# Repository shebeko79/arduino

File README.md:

## Projects description
[Pulmonary Function Testing (PFT)](./pft)

[Car track using telegram bot](./car_dfrobot)

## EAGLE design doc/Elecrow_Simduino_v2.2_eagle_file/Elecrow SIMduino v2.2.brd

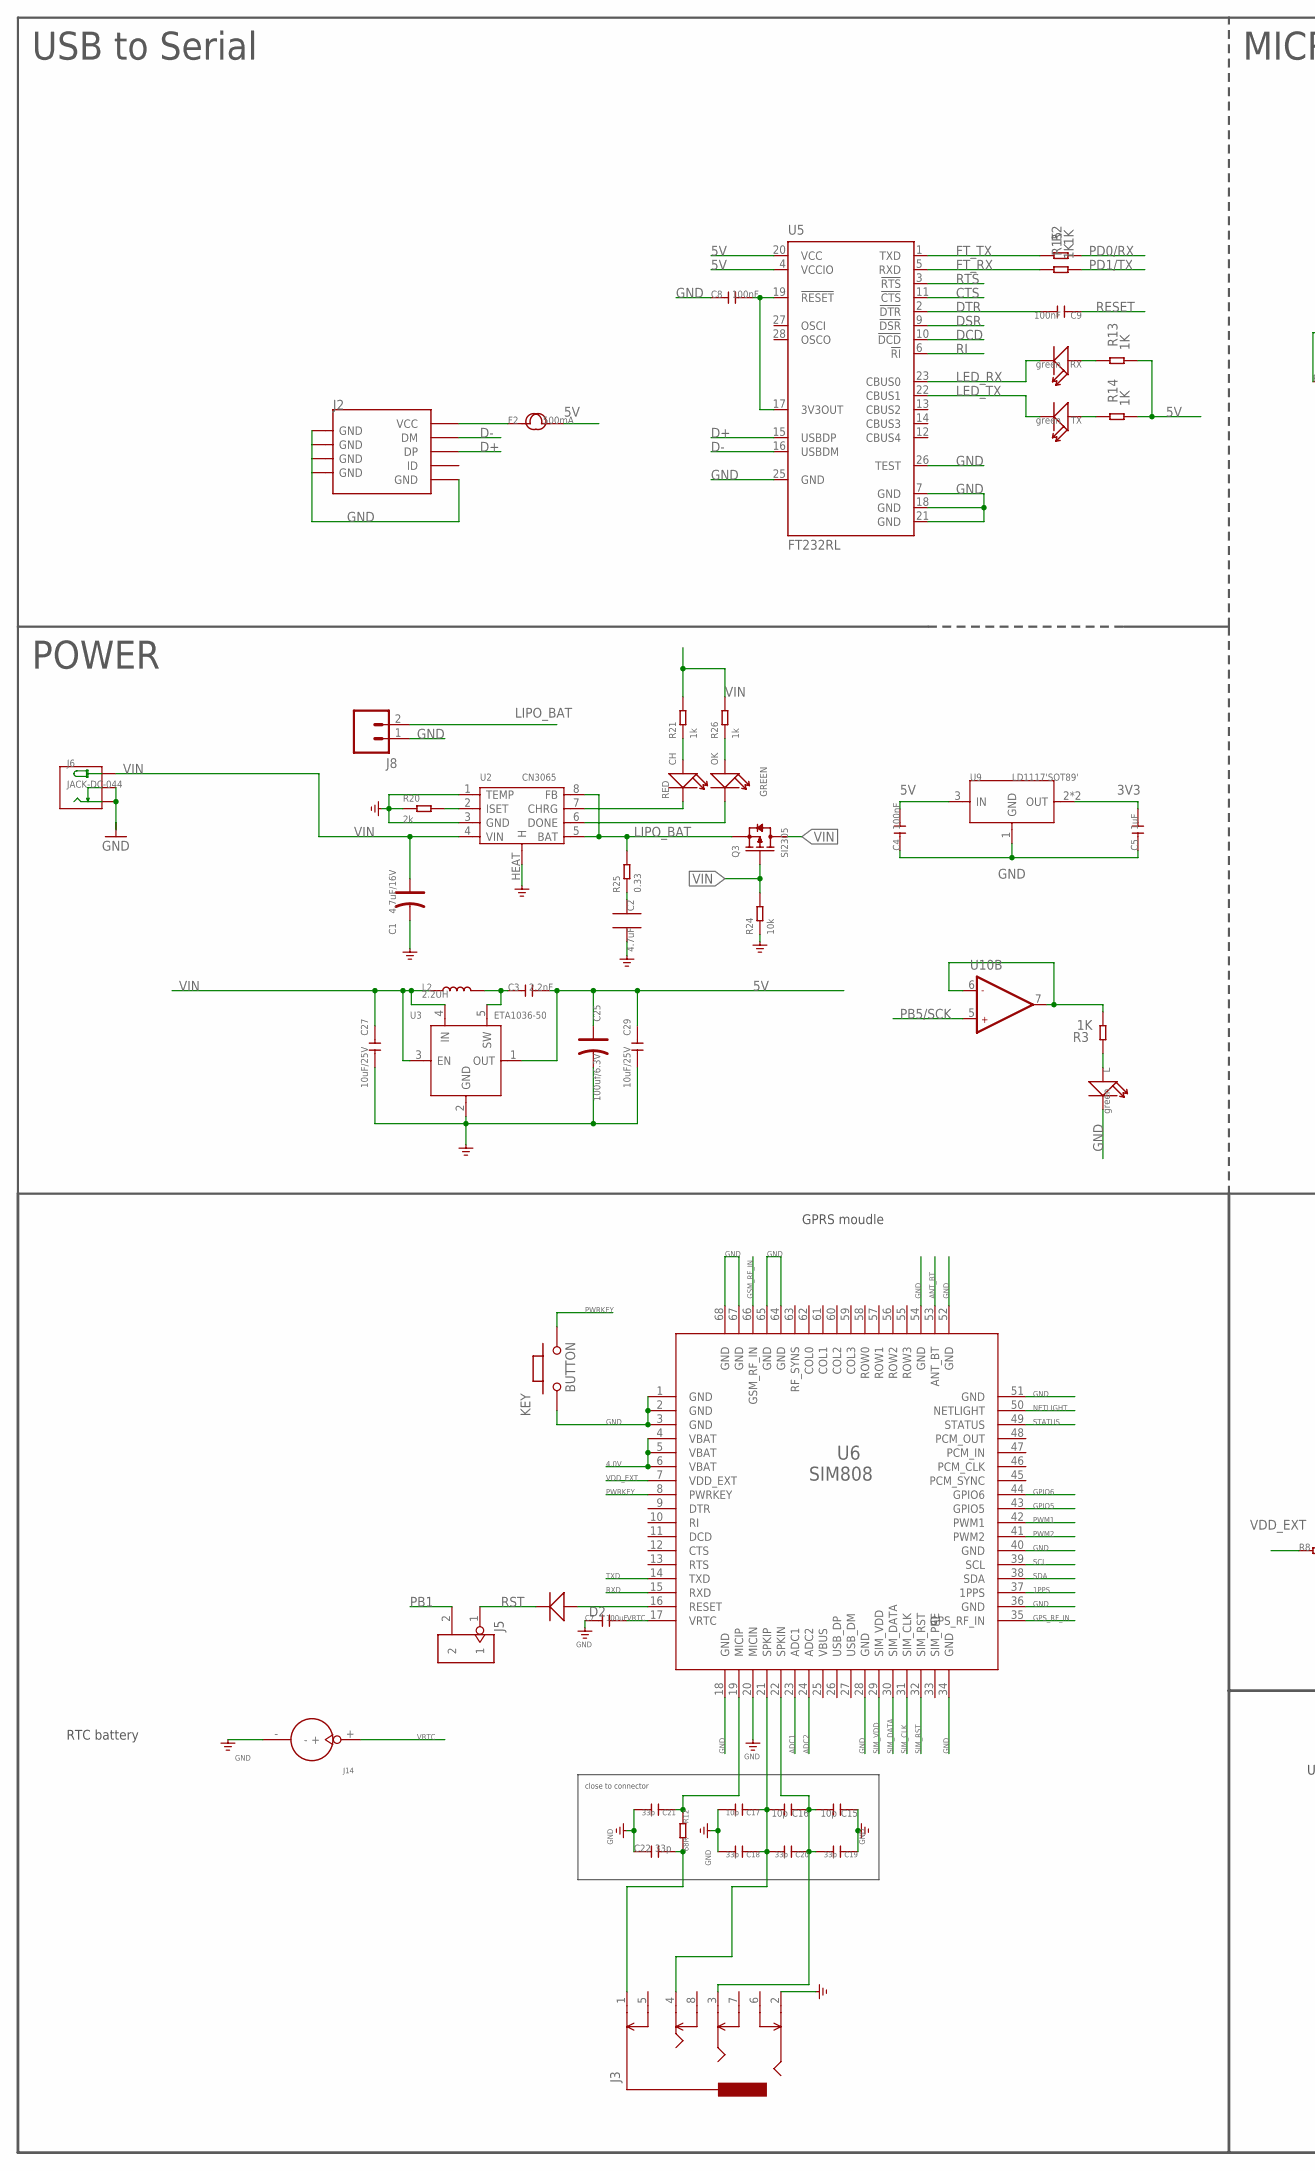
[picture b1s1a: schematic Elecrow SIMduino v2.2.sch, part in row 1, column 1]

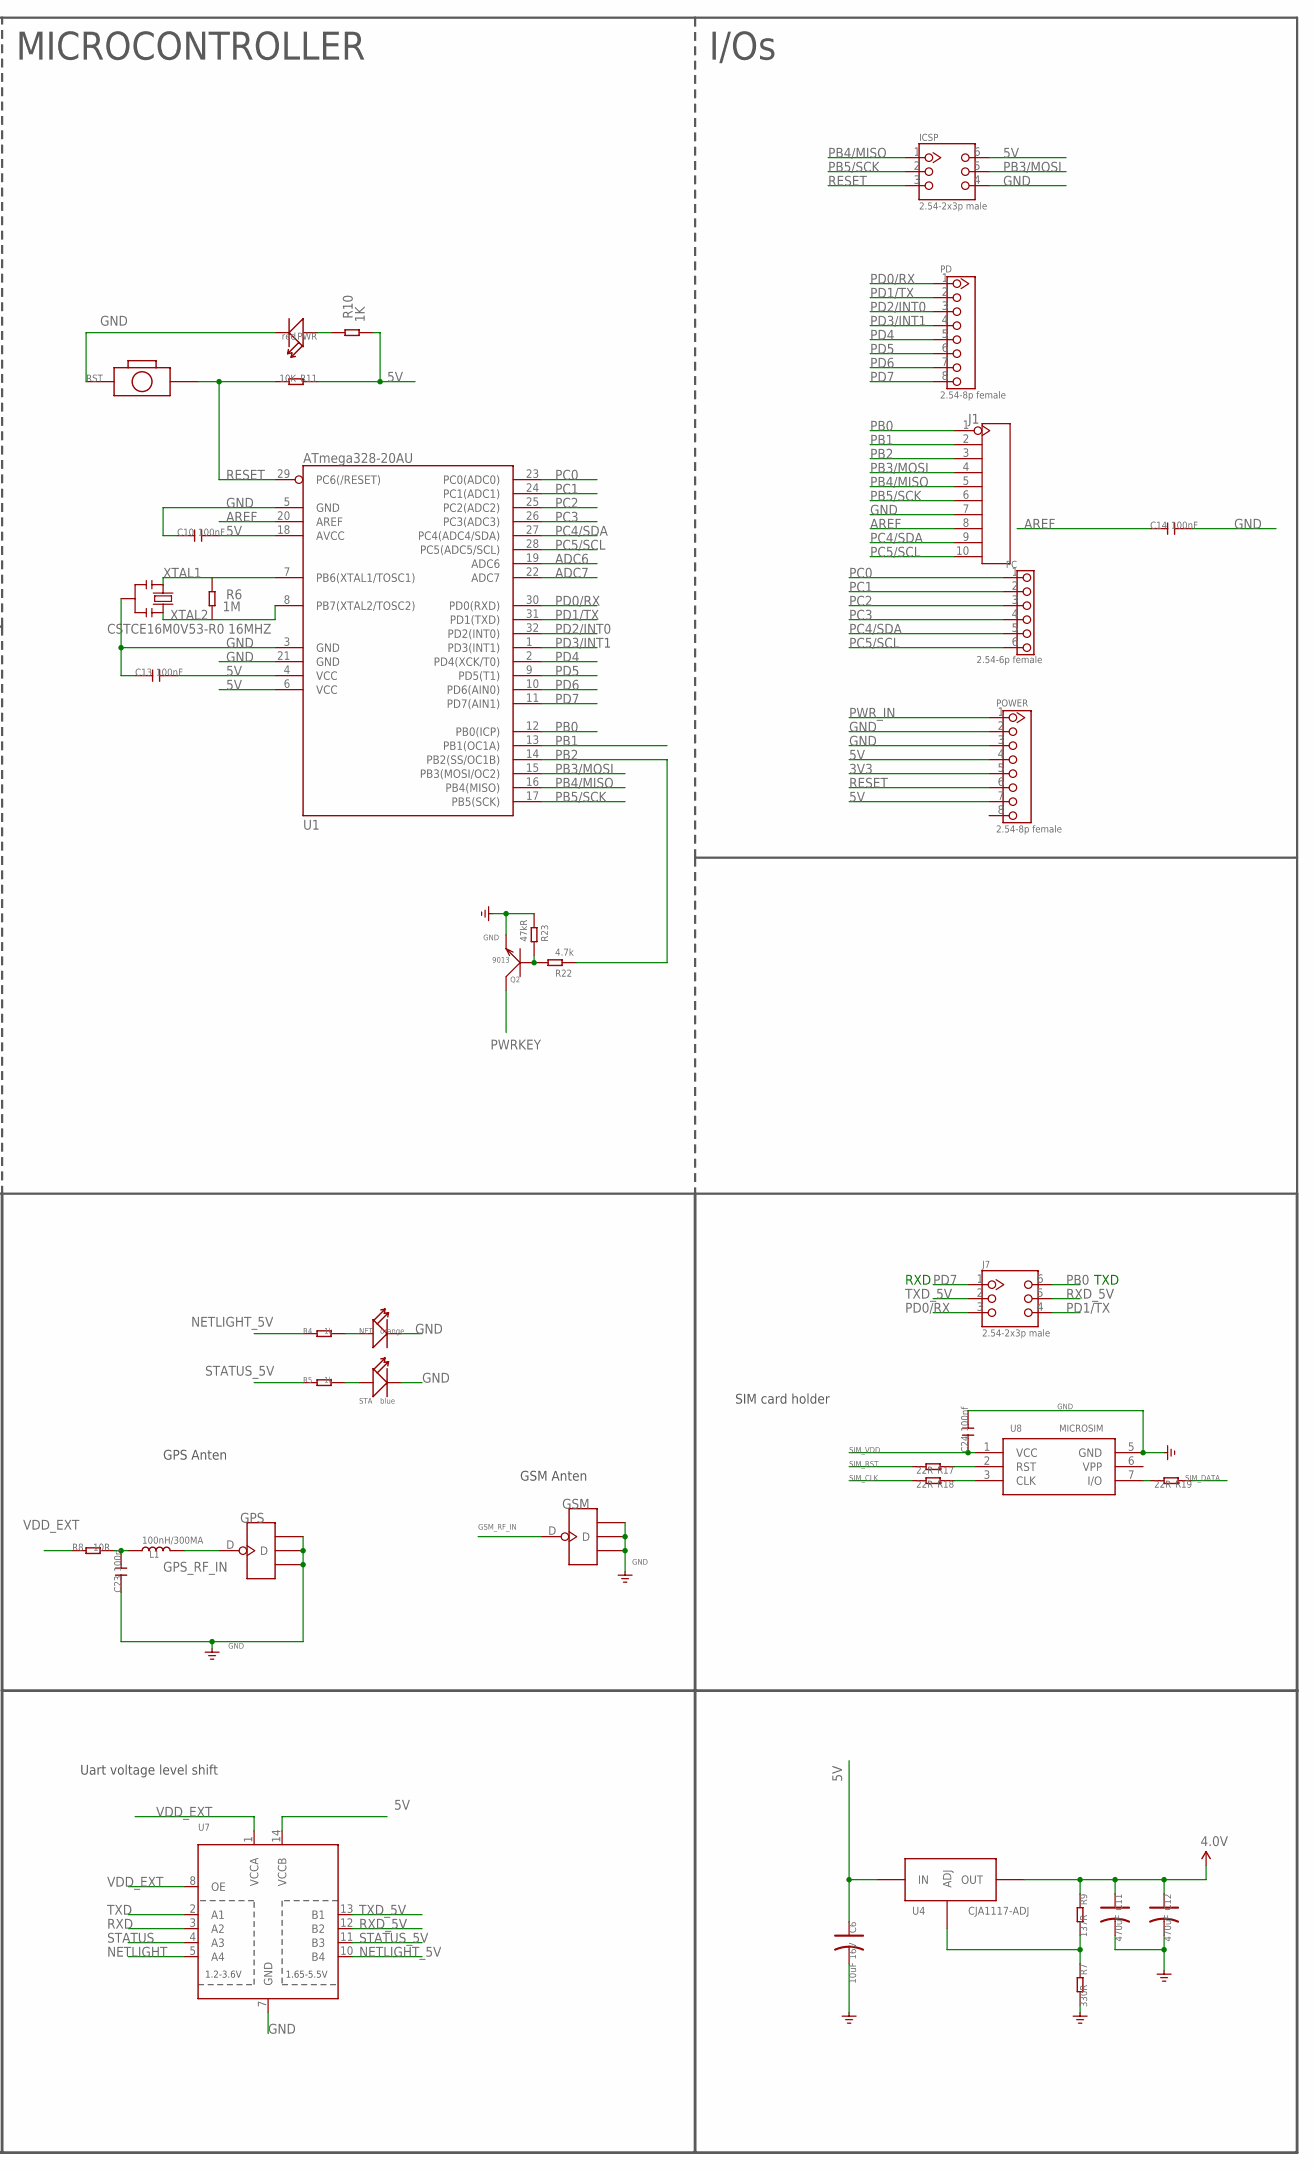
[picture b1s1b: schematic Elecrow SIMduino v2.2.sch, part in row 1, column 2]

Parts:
C1: 4.7uF/16V; AVX_A
C2: 4.7uF; 0805
C3: 2.2nF; C0603
C4, C8, C9, C10, C13, C14: 100nF; C0603
C5: 1uF; C0603
C6: 10uF 16V; AVX-A
C7: 100uF; C0805
C11, C12: 470uF; AVX-D
C15, C16, C17: 10p; C0402
C18, C19, C20: 33p; C0402
C21, C22: 33p; C0603
C23: 100n; C0603
C24: 100nf; C0603
C25: 100uf/6.3V; AVX-B
C27, C29: 10uF/25V; C0805
CH: RED; LED-0603
D2: D'0805'; SOD323
F2: 500mA; R1206@1
GPS: ANTENNA-U-FL; 4P-U-FL
GSM: ANTENNA-U-FL; 4P-U-FL
ICSP: 2.54-2x3p male; 2X3P-2.54
J1: HEADER-10P-2.54; 10P-2.54
J2: USB-MINIUSB-5P-STRONG; MINI-SMD-5P
J3: AUDIO-8P'PJ-3536-L6S'; 8P-3.5-SMD
J5: HEADER-2P-65/35MIL; 2P-2.54-65/35MIL
J6: JACK-DC-044; DC-404
J7: 2.54-2x3p male; 2X3P-2.54
J8: M02-JST-2MM-SMT; JST-2-SMD
J14: HOLDER-BATTERY-2P-CR1220; CR1220
KEY: BUTTON; 157SW
L: green; LED-0603
L1: 100nH/300MA; L0603
L2: 2.2UH; SD32-4R7MC
NET: orange; LED-0603
OK: GREEN; LED-0603
PC: 2.54-6p female; 6P-2.54-65/35MIL
PD: 2.54-8p female; 8P-2.54
POWER: 2.54-8p female; 8P-2.54
PWR: red; LED-0603
Q2: 9013; SOT23
Q3: SI2305; SOT-23
R2, R3, R10, R13, R14, R15: 1K; R0603
R4, R5, R21, R26: 1k; R0603
R6: 1M; R0603
R7: 330R; R0603
R8: 10R; R0603
R9: 137R; R0603
R11: 10K; R0603
R12: 68R; R0603
R17, R18, R19: 22R; R0603
R20: 2k; R0603
R22: 4.7k; R0402
R23: 47kR; R0402
R24: 10k; R0603
R25: 0.33; R0603
RST: BOTTON-2P-90D; 2P-7.62X3.56-90D
RX: green; LED-0603
STA: blue; LED-0603
TX: green; LED-0603
U1: ATmega328-20AU; TQFP32
U2: CN3065; DFN-8
U3: ETA1036-50; SOT23-5
U4: CJA1117-ADJ; SOT89
U5: FT232RL; SSOP28
U6: SIM808
U7: TXB0104PWR; TSSOP14
U8: MICROSIM
U9: LD1117'SOT89'; SOT89
U10: LMV358DGK; MSOP8
Y2: CSTCE16M0V53-R0 16MHZ; RESONATOR

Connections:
1PPS: U6.37 (1PPS)
3V3: C5.2, POWER.5, U9.2 (OUT), U9.4 (OUT)
4.0V: C11.+, C12.+, R9.1, U4.2 (OUT), U4.4 (OUT), U6.4 (VBAT), U6.5 (VBAT), U6.6 (VBAT)
5V: C3.2, C4.2, C6.+, C10.2, C13.2, C25.+, C29.1, F2.2, ICSP.6, POWER.4, POWER.7, R10.1, R11.1, R13.1, R14.1, U1.4 (VCC), U1.6 (VCC), U1.18 (AVCC), U3.1 (OUT), U4.3 (IN), U5.4 (VCCIO), U5.20 (VCC), U7.14 (VCCB), U9.3 (IN)
+V: U10.8 (+V)
ADC1: U6.23 (ADC1)
ADC2: U6.24 (ADC2)
ADC6: U1.19 (ADC6)
ADC7: U1.22 (ADC7)
ANT_BT: U6.53 (ANT_BT)
AREF: C14.1, J1.8, U1.20 (AREF)
COL0: U6.62 (COL0)
COL1: U6.61 (COL1)
COL2: U6.60 (COL2)
COL3: U6.59 (COL3)
CTS: U5.11 (!CTS)
D+: J2.3 (DP), U5.15 (USBDP)
D-: J2.2 (DM), U5.16 (USBDM)
DCD: U5.10 (!DCD)
DSR: U5.9 (!DSR)
DTR: C9.2, U5.2 (!DTR)
FT_RX: R15.2, U5.5 (RXD)
FT_TX: R2.2, U5.1 (TXD)
GND: C1.-, C2.2, C4.1, C5.1, C6.-, C7.1, C8.1, C10.1, C11.-, C12.-, C13.1, C14.2, C15.1, C17.2, C18.2, C19.1, C21.2, C22.1, C23.1, C24.2, C25.-, C27.2, C29.2, GPS.GND1, GPS.GND2, GPS.GND3, GSM.GND1, GSM.GND2, GSM.GND3, ICSP.4, J1.7, J2.5 (GND), J2.GND@1 (GND), J2.GND@2 (GND), J2.GND@3 (GND), J2.GND@4 (GND), J3.2, J6.-, J6.CDN, J8.1, J14.-, KEY.1, L.-, NET.-, POWER.2, POWER.3, PWR.-, Q2.2 (E), R7.2, R20.1, R23.1, R24.1, RST.P$1 (1), STA.-, U1.3 (GND), U1.5 (GND), U1.21 (GND), U2.1 (TEMP), U2.3 (GND), U2.HEAT (H), U3.2 (GND), U5.7 (GND), U5.18 (GND), U5.21 (GND), U5.25 (GND), U5.26 (TEST), U6.1 (GND), U6.2 (GND), U6.3 (GND), U6.18 (GND), U6.20 (MICIN), U6.28 (GND), U6.34 (GND), U6.36 (GND), U6.40 (GND), U6.51 (GND), U6.52 (GND), U6.54 (GND), U6.64 (GND), U6.65 (GND), U6.67 (GND), U6.68 (GND), U7.7 (GND), U8.5 (GND), U9.1 (GND), U10.4 (GND), Y2.2
GPIO5: U6.43 (GPIO5)
GPIO6: U6.44 (GPIO6)
GPS_RF_IN: GPS.D, L1.2, U6.35 (GPS_RF_IN)
GSM_RF_IN: GSM.D, U6.66 (GSM_RF_IN)
LED_RX: RX.-, U5.23 (CBUS0)
LED_TX: TX.-, U5.22 (CBUS1)
LIPO_BAT: J8.2, Q3.2 (S), R25.2, U2.5 (BAT), U2.8 (FB)
unnamed: R20.2, U2.2 (ISET)
unnamed: R13.2, RX.+
unnamed: L.+, R3.2
unnamed: R5.2, STA.+
unnamed: R3.1, U10.6 (-IN2), U10.7 (OUT2)
unnamed: C8.2, U5.17 (3V3OUT), U5.19 (!RESET)
unnamed: PWR.+, R10.2
unnamed: R14.2, TX.+
unnamed: F2.1, J2.1 (VCC)
unnamed: NET.+, R4.2
unnamed: R18.1, U8.3 (CLK)
unnamed: R17.1, U8.2 (RST)
unnamed: C21.1, R12.1, U6.19 (MICIP)
unnamed: C16.2, C17.1, C18.1, C20.2, J3.4, U6.21 (SPKIP)
unnamed: R19.2, U8.7 (I/O)
unnamed: R7.1, R9.2, U4.1 (ADJ)
unnamed: D2.+, U6.16 (RESET)
unnamed: C15.2, C16.1, C19.2, C20.1, J3.3, U6.22 (SPKIN)
unnamed: CH.-, U2.7 (CHRG)
unnamed: C23.2, L1.1, R8.2
unnamed: OK.-, U2.6 (DONE)
unnamed: OK.+, R26.1
unnamed: C2.1, R25.1
unnamed: CH.+, R21.1
unnamed: C3.1, L2.2, U3.5 (SW)
unnamed: C22.2, J3.1, R12.2
unnamed: Q2.1 (B), R22.2, R23.2
NETLIGHT: U6.50 (NETLIGHT), U7.5 (A4)
NETLIGHT_5V: R4.1, U7.10 (B4)
PB0: J1.1, J7.6, U1.12 (PB0(ICP))
PB1: J1.2, J5.2, U1.13 (PB1(OC1A))
PB2: J1.3, R22.1, U1.14 (PB2(SS/OC1B))
PB3/MOSI: ICSP.5, J1.4, U1.15 (PB3(MOSI/OC2))
PB4/MISO: ICSP.1, J1.5, U1.16 (PB4(MISO))
PB5/SCK: ICSP.2, J1.6, U1.17 (PB5(SCK)), U10.5 (+IN2)
PC0: PC.1, U1.23 (PC0(ADC0))
PC1: PC.2, U1.24 (PC1(ADC1))
PC2: PC.3, U1.25 (PC2(ADC2))
PC3: PC.4, U1.26 (PC3(ADC3))
PC4/SDA: J1.9, PC.5, U1.27 (PC4(ADC4/SDA))
PC5/SCL: J1.10, PC.6, U1.28 (PC5(ADC5/SCL))
PD0/RX: J7.3, PD.1, R2.1, U1.30 (PD0(RXD))
PD1/TX: J7.4, PD.2, R15.1, U1.31 (PD1(TXD))
PD2/INT0: PD.3, U1.32 (PD2(INT0))
PD3/INT1: PD.4, U1.1 (PD3(INT1))
PD4: PD.5, U1.2 (PD4(XCK/T0))
PD5: PD.6, U1.9 (PD5(T1))
PD6: PD.7, U1.10 (PD6(AIN0))
PD7: J7.1, PD.8, U1.11 (PD7(AIN1))
PWM1: U6.42 (PWM1)
PWM2: U6.41 (PWM2)
PWRKEY: KEY.2, Q2.3 (C), U6.8 (PWRKEY)
PWR_IN: POWER.1
RESET: C9.1, ICSP.3, POWER.6, R11.2, RST.P$2 (2), U1.29 (PC6(/RESET))
RF_SYNS: U6.63 (RF_SYNS)
RI: U5.6 (!RI)
ROW0: U6.58 (ROW0)
ROW1: U6.57 (ROW1)
ROW2: U6.56 (ROW2)
ROW3: U6.55 (ROW3)
RST: D2.-, J5.1
RTS: U5.3 (!RTS)
RXD: U6.15 (RXD), U7.3 (A2)
RXD_5V: J7.5, U7.12 (B2)
SCL: U6.39 (SCL)
SDA: U6.38 (SDA)
SIM_CLK: R18.2, U6.31 (SIM_CLK)
SIM_DATA: R19.1, U6.30 (SIM_DATA)
SIM_RST: R17.2, U6.32 (SIM_RST)
SIM_VDD: C24.1, U6.29 (SIM_VDD), U8.1 (VCC)
STATUS: U6.49 (STATUS), U7.4 (A3)
STATUS_5V: R5.1, U7.11 (B3)
TXD: U6.14 (TXD), U7.2 (A1)
TXD_5V: J7.2, U7.13 (B1)
VDD_EXT: R8.1, U6.7 (VDD_EXT), U7.1 (VCCA), U7.8 (OE)
VIN: C1.+, C27.1, J6.+, L2.1, Q3.1 (G), Q3.3 (D), R21.2, R24.2, R26.2, U2.4 (VIN), U3.3 (EN), U3.4 (IN)
VRTC: C7.2, J14.+, U6.17 (VRTC)
XTAL1: R6.2, U1.7 (PB6(XTAL1/TOSC1)), Y2.1
XTAL2: R6.1, U1.8 (PB7(XTAL2/TOSC2)), Y2.3

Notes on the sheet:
USB to Serial
POWER
MICROCONTROLLER
I/Os
close to connector
GPRS moudle
GPS Anten
GSM Anten
Uart voltage level shift
SIM card holder
TXD
RXD
RTC battery

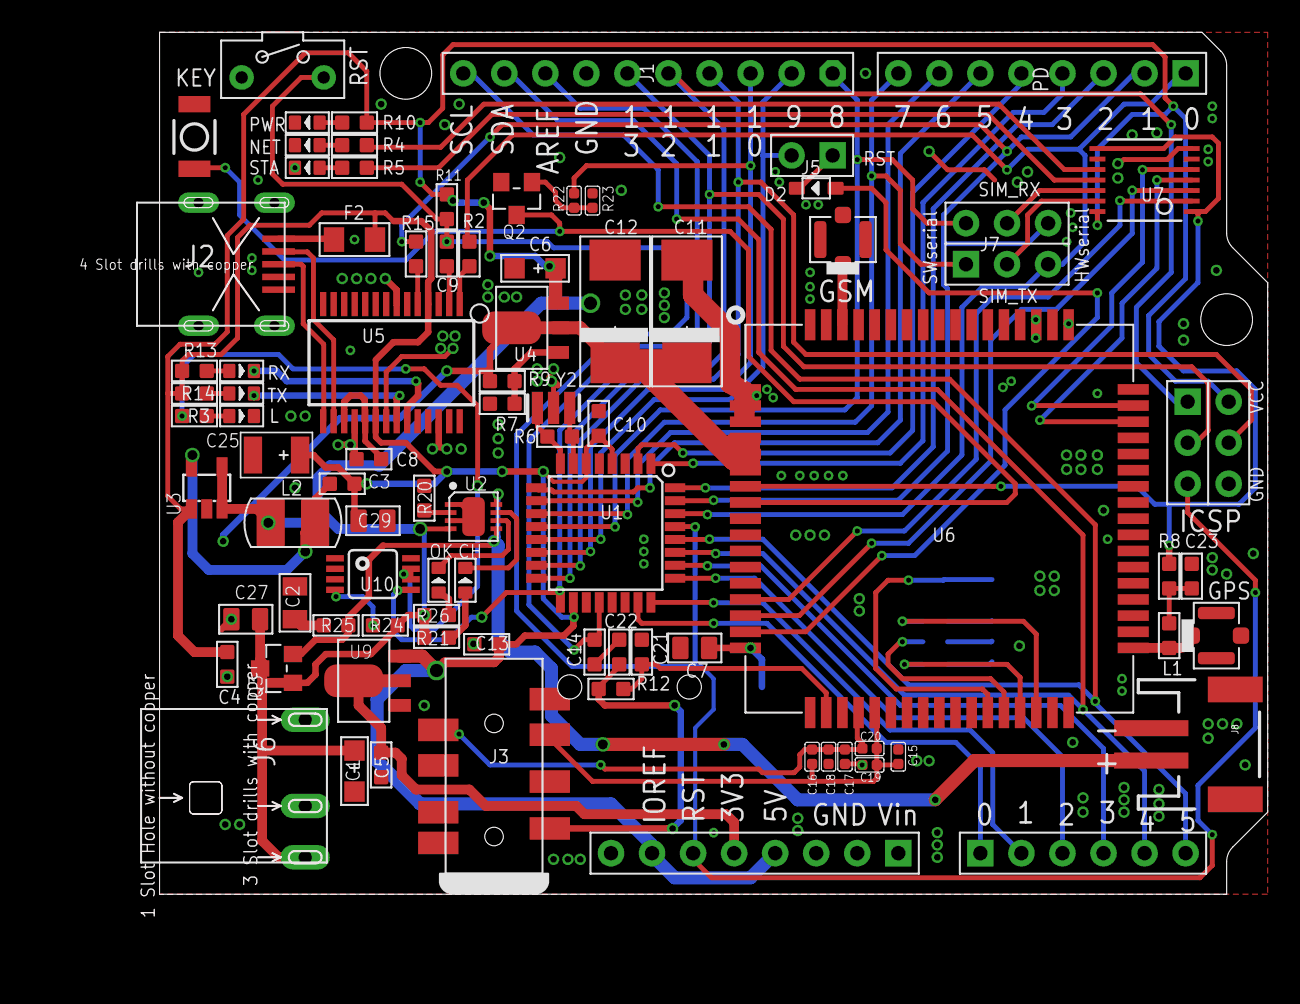
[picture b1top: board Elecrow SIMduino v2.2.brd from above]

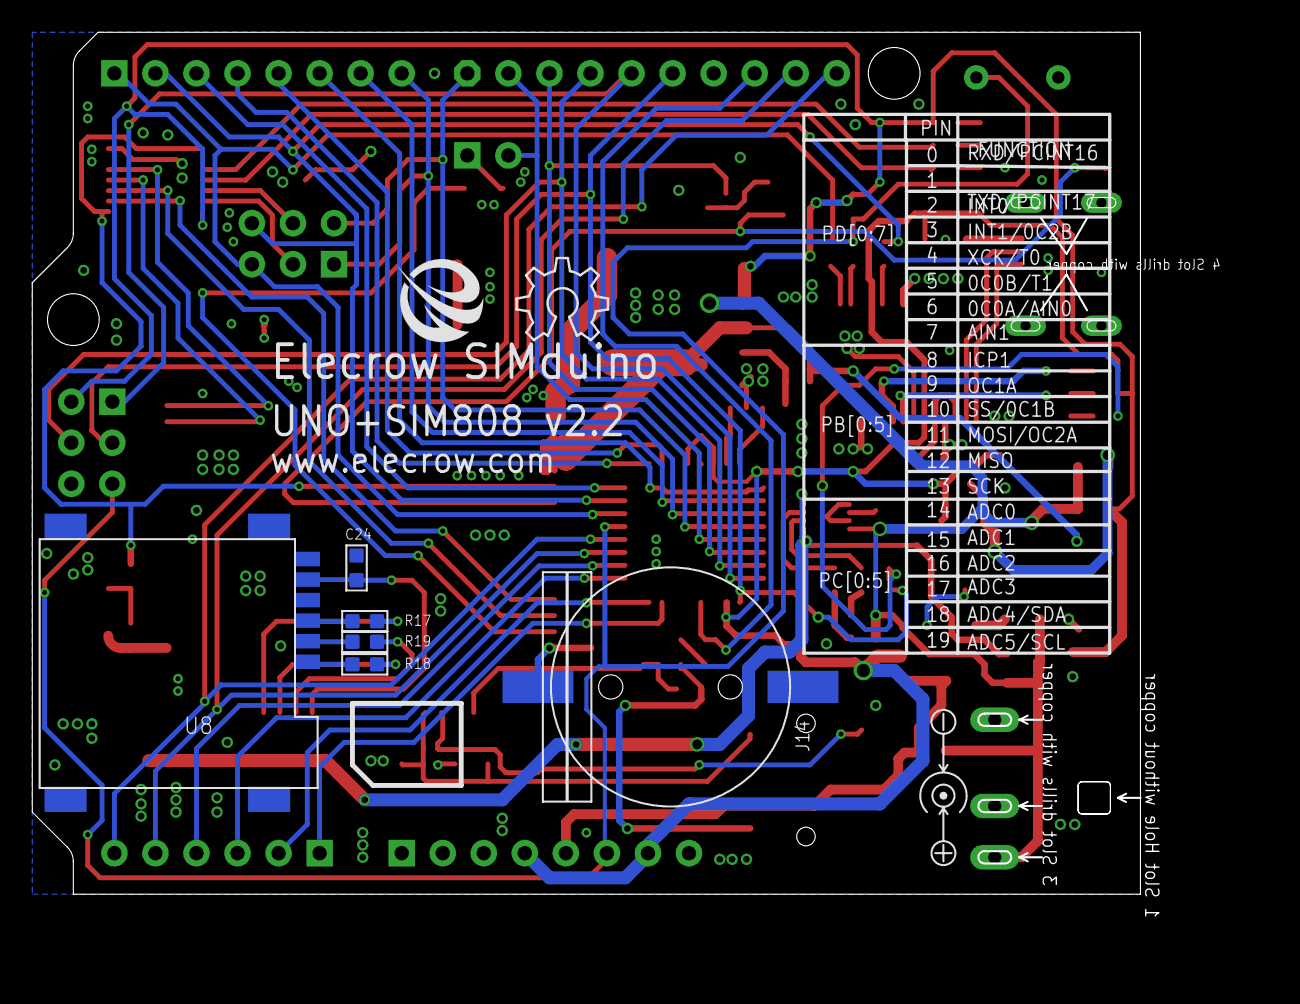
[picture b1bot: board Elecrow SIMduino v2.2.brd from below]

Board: 2 copper layers, 68.6 x 53.3 mm, 94 parts (8 on the bottom side), 82 nets.

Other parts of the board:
U$1: OSHW_6X200_NOTEXT
U$2: ELECROW-NEW

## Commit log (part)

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2021-11-11 add chicken
2021-11-11 add tests
2021-11-11 add doc
2021-11-11 add dachagaraz
2021-11-11 commit others projects
2021-11-11 CmAlarm
2021-12-26 Recover after WiFi failures. Silent messages. Temp sensor temporary doesn't work
2021-12-26 gitignore
2021-12-26 wire_length
2021-12-26 change for esp32
2021-12-26 udp_client
2023-01-16 Add scheme of uno sim800 board
2023-01-17 Files w/o secret keys
2023-02-15 SIM7000 car tracking version
2023-02-15 less debug information
2023-02-15 Just AT command list. Useful for troubleshooting.
2024-03-22 Pulmonary function tests
2024-03-22 Better touch screen interraction Better graph
2024-03-23 ticks[] calculated just in timer scale chart to actual data print seconds in x axis
2024-04-11 Draw battery status
2024-04-11 Add 3d model
2024-04-13 1. Result number on a different screen. 2. Add sleep mode. Sleep mode note that effective, device still consume 8mA so we still need physical power button
2024-04-13 1. Reduce mundshtuk size 2. Add cover to hide electronics
2024-04-13 Add *.blend1 to gitignore
2024-04-13 1. Move tick counter from timer isr to pin isr 2. Reduce scale because free spin was physically removed 3. Shortest scale must be not shorter than 1 second
2024-04-19 Draw total air-flow Draw FVC,FEV1,FEV1/FVC in the results
2024-04-20 Add license and readme
2024-04-20 Add references
2024-04-20 Fix spelling in README.md
2024-04-20 Add demo video to README.md
2024-04-20 Images of device
2024-04-20 Reduce images size
2024-04-20 Add images to README.md
2024-08-30 2 wheel platform based on esp32
2024-09-11 SIM7070 documentation
2024-09-11 Use macro for telegram chat id
2024-09-11 Test sim7070 AT commands sequence
2024-09-11 1. Save certificate into modem 2. Just regular AT terminal
2024-09-11 Prepare for modem replacement Isolate modem header
2024-09-11 Add sim7070.h
2024-09-13 Same speed as debug in car_dfrobot
2024-09-13 Remove comments
2024-09-13 1. Use F() macro to store strings in PROGMEM 2. Rewrite for HTTPS. Still need to debug.
2024-09-13 GPS can't work at the same time with mobile network. See https://stackoverflow.com/questions/61857667/sim7080g-module-cant-send-data-over-tcp-while-using-gnss
    That's why we must switch off GPS and then send data.
    For the same reason we can't keep HTTPS connection and have to open it again for each request.
2024-09-13 1. Read receive buffer chunk-by-chunk 2. use separate buffer for telegram, because modem_answer overrides by commands 3. Push 2 message at start, because first lost anyway 4. Commented out unnecessar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
2024-09-15 Overall projects readme
2024-09-20 Bluetooth remote control
2024-09-28 Add "block" command in BT remote control
2024-09-28 Examples files for maixcam
2024-10-05 Implementing state machine for UI
2024-10-06 Implement button click and rectangle selection
2024-10-06 Add rectangle normalization
2024-10-07 Add MoveTo algo.
2024-10-12 returns image each second on web
2024-10-12 Add buttons using ChatGPT
2024-10-12 ChatGPT button click handler
2024-10-12 chatGPT image click
2024-10-12 chatGPT select rectangle
2024-10-12 1. Prevent rectangle visible until object selection (chatGPT) 2. Prevent dragging image (chatGPT) 3. Process requests on server side 4. Prevent crash, when to_jpeg() returns None after script restart
2024-10-12 Add just move states
2024-10-13 Mobile adaptation for select rectangle (chatGPT)
2024-10-13 Click on image for mobile (chatGPT)
2024-10-13 Move buttons to right
2024-10-13 Rename move states for vertical alignment Load main html from BASE_PATH path
2024-10-15 Add WiFi features. If fail connect to WiFi switch to AP mode
2024-10-16 Disable wifi switch AP mode doesn't start DHCP And switch back to STA go wrong.
2024-10-19 Configuring network thru python was bad idea. Add S30wifidyn which try establish sta connection, if fails switch to ap mode
2024-10-19 Shrink move state to fit on a screen More robust S81robot stop function
2024-10-27 1. Get rid of Flask, because it creates a lot of threads and to noisy 2. Implement synchronized function call in main thread. 3. Get state just after click,click_point, sel_rect requests
2024-10-27 1. Apply immediately /click /click_point /sel_rect to buttons state 2. Return state even if requests are not executed 3. Move server to 80 port
2024-11-09 Increase line width to avoid red-grey rectangles
2024-11-19 pan\tilt stl model
2024-12-08 Parts schematic
2024-12-08 Test of zs-x11h controller
2024-12-09 rename motor.h to mdd3a controller which was used to control dc motor
2024-12-09 Add szx11h motor controller
2024-12-10 1. Move to PlatformIO 2. Speed measurement
2024-12-11 Connect brake pin
2024-12-12 Add PID control
2024-12-12 Change remote to relative protocol
2024-12-12 Add relative protocol
2024-12-13 1. Always brake for zero speed 2. 20kHz PWM just follow controllers recommendations 3. Separate RELATIVE_MAX_SPEED because it a bit scary with full speed 4. Dump wheels state in com port to have a gl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
2024-12-13 command to set maximum relative_speed
2024-12-13 Better command parsing
2024-12-21 Update 3d models 1. Base for pantilt 2. Cover for 2020 profile
2024-12-21 shorter screw placeholer
2024-12-25 Move servo closer to the front
2024-12-25 Maixcam pinout
2024-12-28 Fix rotation cast
2024-12-28 Change mover to speed and pan
2024-12-31 Add scservo_sdk and pan_tilt example proba/pan_tilt.py all necessary function (i.e. reduce baud rate) which performes thru USB of SCServo controller maix/pan_tilt.py is a sketch for pan-til support
2025-01-01 Implementation of pan-tilt tracking Doesn't work as expected yet
2025-01-01 Add exit state for graceful exit
2025-01-02 Release servos when exit Measure real focus distance
2025-01-04 Full screen image
2025-01-05 1. Use relative (0.0-1.0) image coordinates for tracker 2. Make image full-screen on http page
2025-01-07 1. Increase camera resolution 2. Add keyboard support to control camera and movement 3. Add Pan state for mobile
2025-01-27 rtsp test
2025-01-27 Avoid low power exception on shutdown
2025-01-27 send file feature Potentially unsafe we need to check if file really in assets directory
2025-02-16 PID control on pwm instead of speed
2025-02-16 Split motor_speed.h to .cpp and .h
2025-02-16 Try to make remote more stable
2025-02-16 Assume we have some koef. between PWM and unloaded wheel speed. Make error correction around this value. Also introduced delays. But it doesn't look like it helps somehow. Add maximum acceleration bu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
2025-02-16 Motors control in separate thread
2025-03-08 Speed test with different masses and PWM
2025-03-13 Yet another speed control. Based on equilibrium velocity. Still not satisfied how it's work
2025-03-14 Temoprary checkpoint
2025-03-15 Less or more satisfied. Works pretty much the same for different loads. Like empty truck or me as a load. We don't try to adjust m_speed2pwm because it not constant even for the same environment. In 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
    The general idea now is:
    - adjust PWM slowly unless it increase the speed with any acceleration
    - add one time kick to PWM if speed remain zero
    - break if speed go to far in wrong direction or go with acceleration
2025-03-22 rename timer0 to speed_timer
2025-03-22 Increase pan/tilt insensitive zone to avoid shaking
2025-03-30 Yolo custom model track
2025-04-19 Hide internal tracker structure
2025-04-19 Implement yolo trackers
2025-04-21 Add pan, move, follow tracking modes.
2025-04-21 Caption for tracker selection
2025-04-21 Rename room to yolo
2025-04-21 Show click caption and rectangle caption in HTML
2025-04-21 Fix X offset in point and rectangle selection. Wrong condition cause default 640X480 doesn't update to real size 640X640
2025-04-21 Fix nanotrack display on the screen
2025-04-23 1. Pass correct fit to MoveTo 2. Ensure tracker still in the yolo_trackers, because self stopping algo calls YoloTrackObject::stop() 2 times.
2025-09-29 Test of MOSFET switch
2025-09-29 Discover different streaming options
2025-09-29 Kikad board of the robot
2025-09-29 Moved to https://github.com/shebeko79/robocart.git
2025-10-12 Test of speed and accuracy of ESP ADC
2025-11-29 Few tests
2026-05-07 Moved to robocart project

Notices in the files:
parts and their libraries:
Aesthetics: Licensing: Creative Commons ShareAlike 4.0 International - https://creativecommons.org/licenses/by-sa/4.0
